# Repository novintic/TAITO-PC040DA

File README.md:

A reproduction of the TAITO PC040DA digital-to-analog converter hybrids used in the videocircuitry on some TAITO boards like Bubble Bobble.

the simpler version uses a weighted resistor- network with more or less common values. It works well on Bubble Bobble.

There's also a version with an OPamp to amplify the output. This version has not really been tested as the one without seems to just work well..

Please understand that we are not able to offer any support. Use at your own risk. Thank you.

NOVINTIC 2026

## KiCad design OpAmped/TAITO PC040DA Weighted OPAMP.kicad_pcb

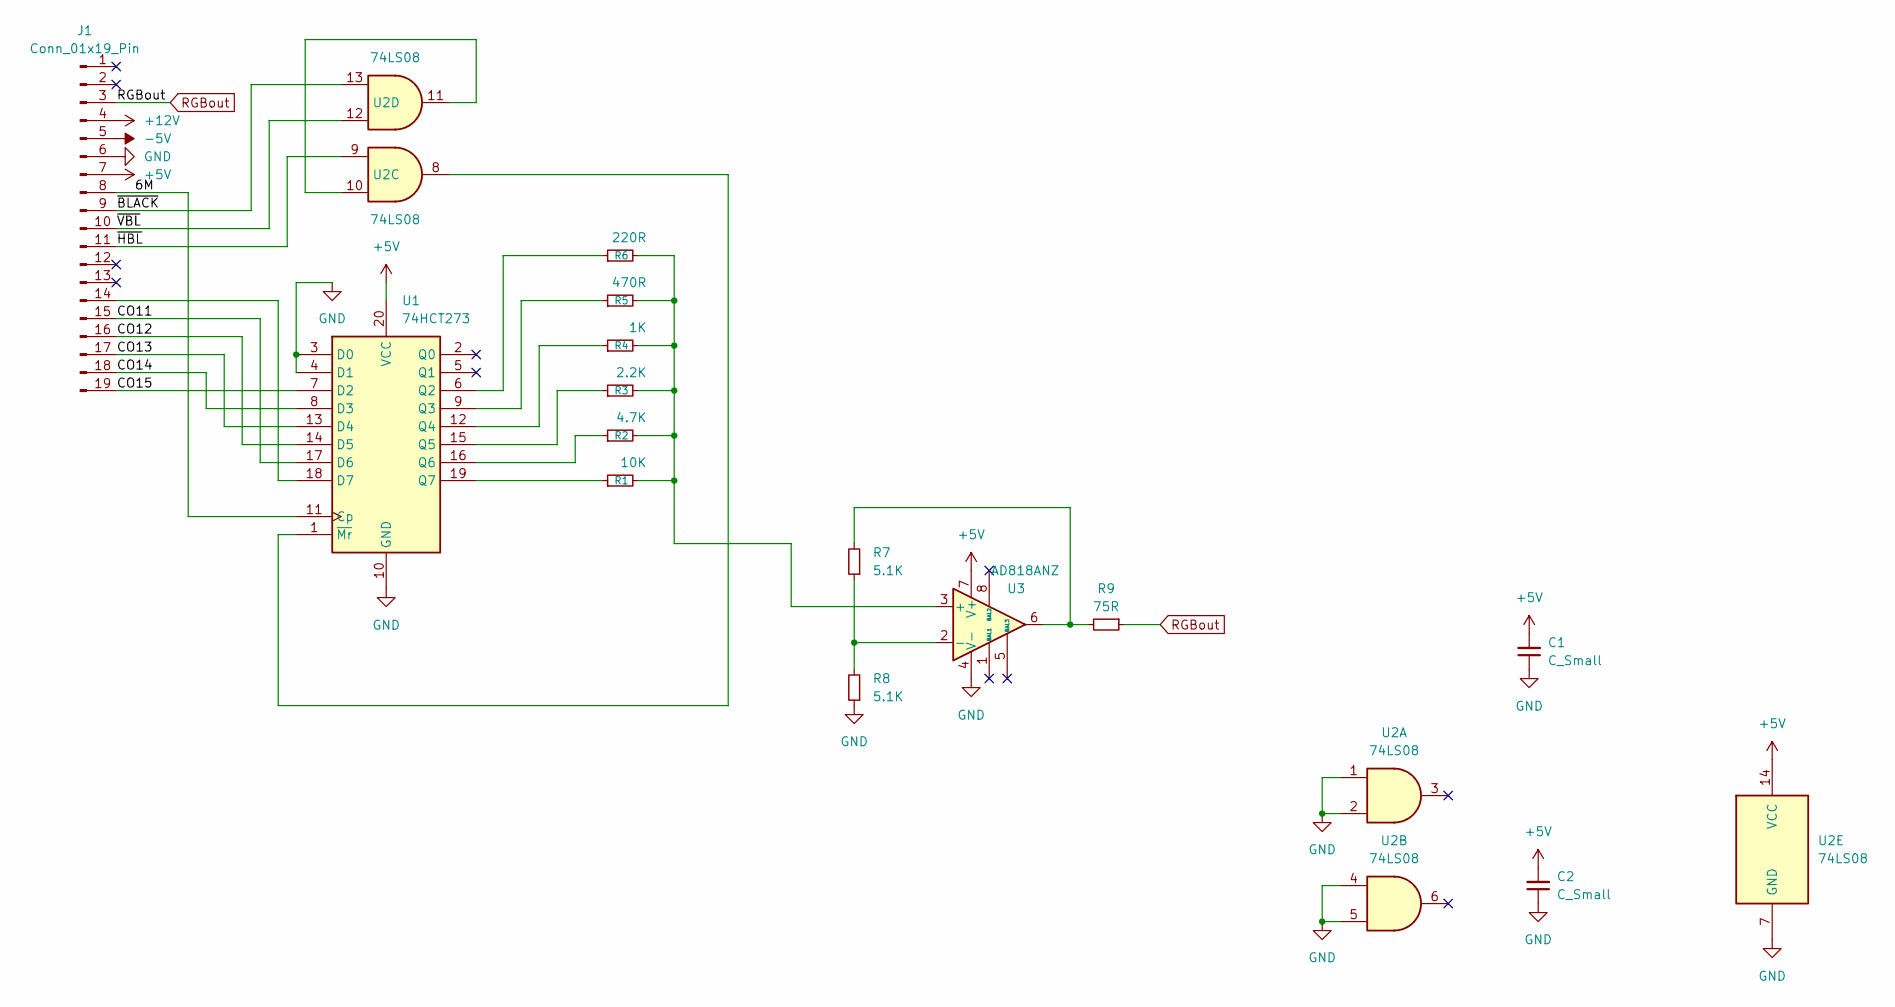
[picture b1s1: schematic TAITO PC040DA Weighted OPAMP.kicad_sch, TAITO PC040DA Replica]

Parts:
C1, C2: C_Small; C_0805_2012Metric_Pad1.18x1.45mm_HandSolder
J1: Conn_01x19_Pin; PinHeader_1x19_P2.54mm_Vertical
R1: 10K; R_0805_2012Metric_Pad1.20x1.40mm_HandSolder
R2: 4.7K; R_0805_2012Metric_Pad1.20x1.40mm_HandSolder
R3: 2.2K; R_0805_2012Metric_Pad1.20x1.40mm_HandSolder
R4: 1K; R_0805_2012Metric_Pad1.20x1.40mm_HandSolder
R5: 470R; R_0805_2012Metric_Pad1.20x1.40mm_HandSolder
R6: 220R; R_0805_2012Metric_Pad1.20x1.40mm_HandSolder
R7, R8: 5.1K; R_0805_2012Metric_Pad1.20x1.40mm_HandSolder; LCSC C26023
R9: 75R; R_0805_2012Metric_Pad1.20x1.40mm_HandSolder; LCSC C431854
U1: 74HCT273; TSSOP-20_4.4x6.5mm_P0.65mm
U2: 74LS08; SOIC-14_3.9x8.7mm_P1.27mm
U3: AD818ANZ; SOIC-8_3.9x4.9mm_P1.27mm; LCSC C128749

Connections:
+5V: C1.2, C2.2, J1.7, U1.20 (VCC), U2.14 (VCC), U3.7 (V+)
+12V: J1.4
-5V: J1.5
/6M: J1.8, U1.11 (Cp)
/CO11: J1.15, U1.17 (D6)
/CO12: J1.16, U1.14 (D5)
/CO13: J1.17, U1.13 (D4)
/CO14: J1.18, U1.8 (D3)
/CO15: J1.19, U1.7 (D2)
/~BLACK: J1.9, U2.13
/~HBL: J1.11, U2.9
/~VBL: J1.10, U2.12
GND: C1.1, C2.1, J1.6, R8.1, U1.3 (D0), U1.4 (D1), U1.10 (GND), U2.1, U2.2, U2.4, U2.5, U2.7 (GND), U3.4 (V-)
unnamed: J1.14, U1.18 (D7)
unnamed: R7.2, R9.2, U3.6
unnamed: R6.1, U1.6 (Q2)
unnamed: R5.1, U1.9 (Q3)
unnamed: R4.1, U1.12 (Q4)
unnamed: R3.1, U1.15 (Q5)
unnamed: R2.1, U1.16 (Q6)
unnamed: R1.1, U1.19 (Q7)
unnamed: U1.1 (~Mr), U2.8
unnamed: U2.10, U2.11
unnamed: R1.2, R2.2, R3.2, R4.2, R5.2, R6.2, U3.3 (+)
unnamed: R7.1, R8.2, U3.2 (-)
RGBout: J1.3, R9.1; also elsewhere on the board

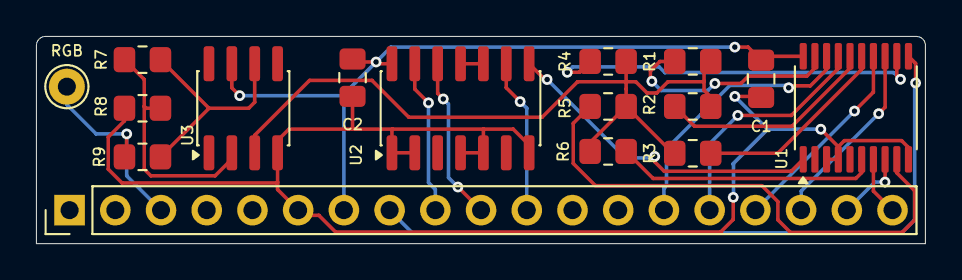
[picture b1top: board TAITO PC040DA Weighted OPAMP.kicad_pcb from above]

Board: 2 copper layers, 49.4 x 11.5 mm, 16 parts (0 on the bottom side), 24 nets.

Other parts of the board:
RGB: TestPoint_THTPad_D2.0mm_Drill1.0mm

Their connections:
RGBout: RGB.1; also elsewhere on the board
